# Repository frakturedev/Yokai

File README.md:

# Yokai
Yokai keyboard, a split keyboard with 5*7 column staggered keys.  Like Corne/Sofle but bigger and worse.

Most recent significant changes - Increased pinky stagger and added an additional thumb key.

Hopefully it will look a little like this:

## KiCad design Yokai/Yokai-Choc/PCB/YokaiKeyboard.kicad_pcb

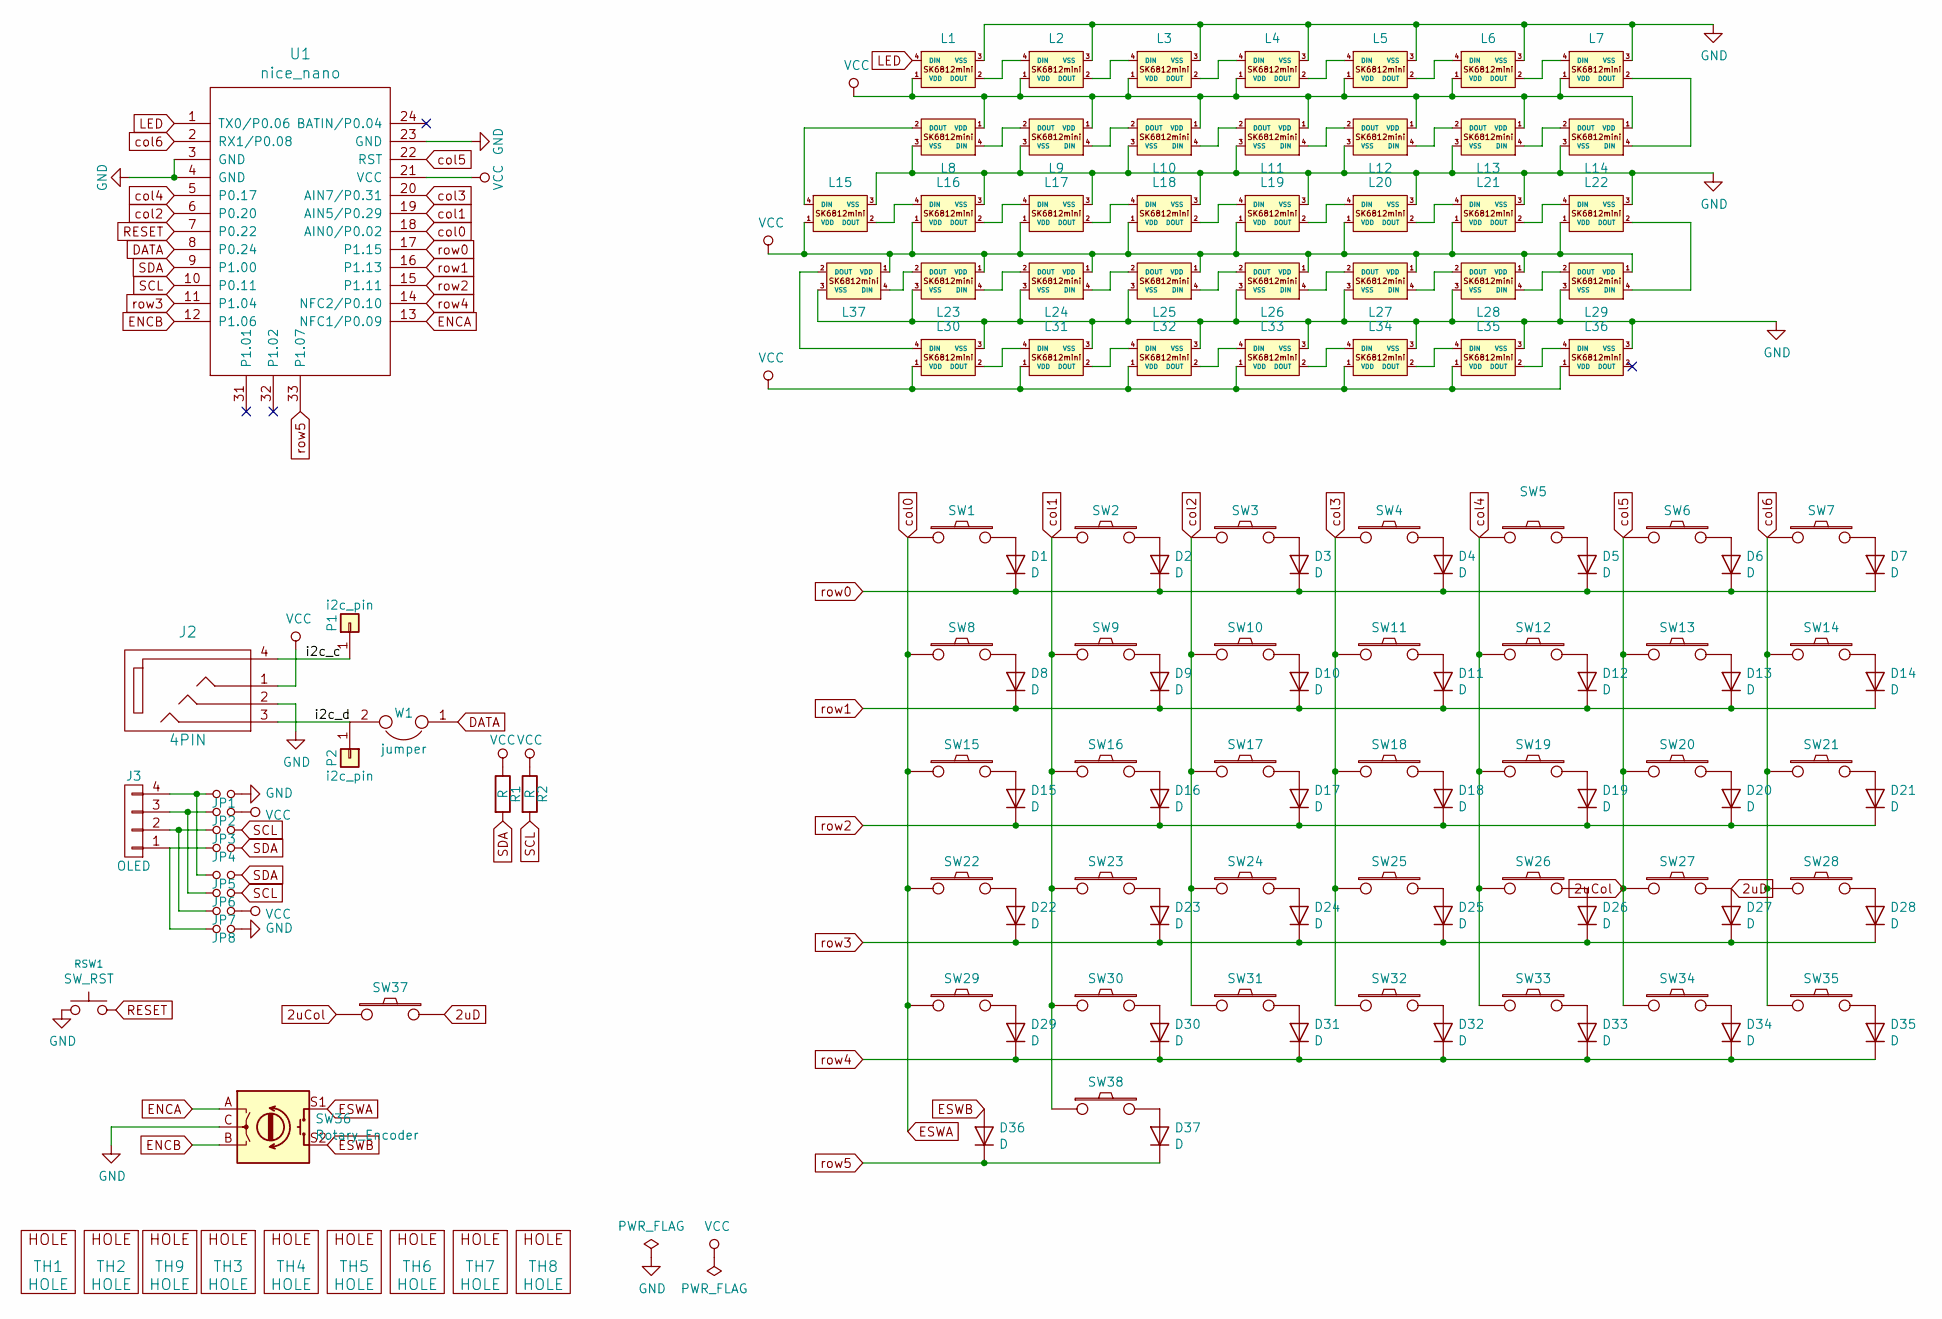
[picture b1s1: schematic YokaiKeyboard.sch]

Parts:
D1, D2, D3, D4, D5, D6, D7, D8, D9, D10, D11, D12, D13, D14, D15, D16, D17, D18, D19, D20, D21, D22, D23, D24, D25, D26, D27, D28, D29, D30, D31, D32, D33, D34, D35, D36, D37: D; smd_diode
J2: 4PIN; MJ-4PP-9
J3: OLED; OLED_4Pin
JP1, JP2, JP3, JP4, JP5, JP6, JP7, JP8: Jumper_NO_Small; Jumper
L1, L2, L3, L4, L5, L6, L7, L8, L9, L10, L11, L12, L13, L14, L15, L16, L17, L18, L19, L20, L21, L22, L23, L24, L25, L26, L27, L28, L29, L30, L31, L32, L33, L34, L35, L36, L37: LED_sk2812_SM; YS-SK6812MINI-E-DoubleSide
P1, P2: i2c_pin; 1pin_conn
R1, R2: R; RESISTOR_mini
RSW1: SW_RST; TACT_SWITCH_TVBP06
SW1, SW2, SW3, SW4, SW5, SW6, SW7, SW8, SW9, SW10, SW11, SW12, SW13, SW14, SW15, SW16, SW17, SW18, SW19, SW20, SW21, SW22, SW23, SW24, SW25, SW26, SW27, SW28, SW29, SW30, SW31, SW32, SW33, SW34, SW35, SW37, SW38: SW_PUSH-MX_W_LED; Choc_Hotswap_DoubleSide
SW36: Rotary_Encoder; RotaryEncoder_Alps_EC11E-Switch_Vertical_H20mm
TH1, TH2, TH9: HOLE; M2_HOLE_PCB
TH3, TH4, TH5, TH6, TH7, TH8: HOLE; HOLE_M2_TH
U1: nice_nano
W1: jumper; Jumper

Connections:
2uCol: SW6.1, SW13.1, SW20.1, SW27.1, SW34.1, SW37.1, U1.22 (RST)
2uD: D27.2 (A), SW27.2, SW37.2
/i2c_c: J2.4, P1.1
/i2c_d: J2.3, P2.1, W1.2
DATA: U1.8 (P0.24), W1.1
ENCA: SW36.A, U1.13 (NFC1/P0.09)
ENCB: SW36.B, U1.12 (P1.06)
ESWA: SW1.1, SW8.1, SW15.1, SW22.1, SW29.1, SW36.S1, U1.18 (AIN0/P0.02)
ESWB: D36.2 (A), SW36.S2
GND: J2.2, JP1.2, JP8.2, L1.3 (VSS), L2.3 (VSS), L3.3 (VSS), L4.3 (VSS), L5.3 (VSS), L6.3 (VSS), L7.3 (VSS), L8.3 (VSS), L9.3 (VSS), L10.3 (VSS), L11.3 (VSS), L12.3 (VSS), L13.3 (VSS), L14.3 (VSS), L15.3 (VSS), L16.3 (VSS), L17.3 (VSS), L18.3 (VSS), L19.3 (VSS), L20.3 (VSS), L21.3 (VSS), L22.3 (VSS), L23.3 (VSS), L24.3 (VSS), L25.3 (VSS), L26.3 (VSS), L27.3 (VSS), L28.3 (VSS), L29.3 (VSS), L30.3 (VSS), L31.3 (VSS), L32.3 (VSS), L33.3 (VSS), L34.3 (VSS), L35.3 (VSS), L36.3 (VSS), L37.3 (VSS), RSW1.1, SW36.C, U1.3 (GND), U1.4 (GND), U1.23 (GND)
LED: L1.4 (DIN), U1.1 (TX0/P0.06)
unnamed: D1.2 (A), SW1.2
unnamed: D2.2 (A), SW2.2
unnamed: D3.2 (A), SW3.2
unnamed: D4.2 (A), SW4.2
unnamed: D5.2 (A), SW5.2
unnamed: D6.2 (A), SW6.2
unnamed: D7.2 (A), SW7.2
unnamed: D8.2 (A), SW8.2
unnamed: D9.2 (A), SW9.2
unnamed: D10.2 (A), SW10.2
unnamed: D11.2 (A), SW11.2
unnamed: D12.2 (A), SW12.2
unnamed: D13.2 (A), SW13.2
unnamed: D14.2 (A), SW14.2
unnamed: D15.2 (A), SW15.2
unnamed: D16.2 (A), SW16.2
unnamed: D17.2 (A), SW17.2
unnamed: D18.2 (A), SW18.2
unnamed: D19.2 (A), SW19.2
unnamed: D20.2 (A), SW20.2
unnamed: D21.2 (A), SW21.2
unnamed: D22.2 (A), SW22.2
unnamed: D23.2 (A), SW23.2
unnamed: D24.2 (A), SW24.2
unnamed: D25.2 (A), SW25.2
unnamed: D26.2 (A), SW26.2
unnamed: D28.2 (A), SW28.2
unnamed: D29.2 (A), SW29.2
unnamed: D30.2 (A), SW30.2
unnamed: D31.2 (A), SW31.2
unnamed: D32.2 (A), SW32.2
unnamed: D33.2 (A), SW33.2
unnamed: D34.2 (A), SW34.2
unnamed: D35.2 (A), SW35.2
unnamed: D37.2 (A), SW38.2
unnamed: J3.1, JP4.1, JP8.1
unnamed: J3.2, JP3.1, JP7.1
unnamed: J3.3, JP2.1, JP6.1
unnamed: J3.4, JP1.1, JP5.1
unnamed: L1.2 (DOUT), L2.4 (DIN)
unnamed: L2.2 (DOUT), L3.4 (DIN)
unnamed: L3.2 (DOUT), L4.4 (DIN)
unnamed: L4.2 (DOUT), L5.4 (DIN)
unnamed: L5.2 (DOUT), L6.4 (DIN)
unnamed: L6.2 (DOUT), L7.4 (DIN)
unnamed: L8.4 (DIN), L9.2 (DOUT)
unnamed: L9.4 (DIN), L10.2 (DOUT)
unnamed: L10.4 (DIN), L11.2 (DOUT)
unnamed: L11.4 (DIN), L12.2 (DOUT)
unnamed: L12.4 (DIN), L13.2 (DOUT)
unnamed: L13.4 (DIN), L14.2 (DOUT)
unnamed: L7.2 (DOUT), L14.4 (DIN)
unnamed: L15.2 (DOUT), L16.4 (DIN)
unnamed: L8.2 (DOUT), L15.4 (DIN)
unnamed: L16.2 (DOUT), L17.4 (DIN)
unnamed: L17.2 (DOUT), L18.4 (DIN)
unnamed: L18.2 (DOUT), L19.4 (DIN)
unnamed: L19.2 (DOUT), L20.4 (DIN)
unnamed: L20.2 (DOUT), L21.4 (DIN)
unnamed: L21.2 (DOUT), L22.4 (DIN)
unnamed: L22.2 (DOUT), L29.4 (DIN)
unnamed: L23.2 (DOUT), L37.4 (DIN)
unnamed: L23.4 (DIN), L24.2 (DOUT)
unnamed: L24.4 (DIN), L25.2 (DOUT)
unnamed: L25.4 (DIN), L26.2 (DOUT)
unnamed: L26.4 (DIN), L27.2 (DOUT)
unnamed: L27.4 (DIN), L28.2 (DOUT)
unnamed: L28.4 (DIN), L29.2 (DOUT)
unnamed: L30.2 (DOUT), L31.4 (DIN)
unnamed: L30.4 (DIN), L37.2 (DOUT)
unnamed: L31.2 (DOUT), L32.4 (DIN)
unnamed: L32.2 (DOUT), L33.4 (DIN)
unnamed: L33.2 (DOUT), L34.4 (DIN)
unnamed: L34.2 (DOUT), L35.4 (DIN)
unnamed: L35.2 (DOUT), L36.4 (DIN)
RESET: RSW1.2, U1.7 (P0.22)
SCL: JP3.2, JP6.2, R2.2, U1.10 (P0.11)
SDA: JP4.2, JP5.2, R1.2, U1.9 (P1.00)
VCC: J2.1, JP2.2, JP7.2, L1.1 (VDD), L2.1 (VDD), L3.1 (VDD), L4.1 (VDD), L5.1 (VDD), L6.1 (VDD), L7.1 (VDD), L8.1 (VDD), L9.1 (VDD), L10.1 (VDD), L11.1 (VDD), L12.1 (VDD), L13.1 (VDD), L14.1 (VDD), L15.1 (VDD), L16.1 (VDD), L17.1 (VDD), L18.1 (VDD), L19.1 (VDD), L20.1 (VDD), L21.1 (VDD), L22.1 (VDD), L23.1 (VDD), L24.1 (VDD), L25.1 (VDD), L26.1 (VDD), L27.1 (VDD), L28.1 (VDD), L29.1 (VDD), L30.1 (VDD), L31.1 (VDD), L32.1 (VDD), L33.1 (VDD), L34.1 (VDD), L35.1 (VDD), L36.1 (VDD), L37.1 (VDD), R1.1, R2.1, U1.21 (VCC)
col1: SW2.1, SW9.1, SW16.1, SW23.1, SW30.1, SW38.1, U1.19 (AIN5/P0.29)
col2: SW3.1, SW10.1, SW17.1, SW24.1, SW31.1, U1.6 (P0.20)
col3: SW4.1, SW11.1, SW18.1, SW25.1, SW32.1, U1.20 (AIN7/P0.31)
col4: SW5.1, SW12.1, SW19.1, SW26.1, SW33.1, U1.5 (P0.17)
col6: SW7.1, SW14.1, SW21.1, SW28.1, SW35.1, U1.2 (RX1/P0.08)
row0: D1.1 (K), D2.1 (K), D3.1 (K), D4.1 (K), D5.1 (K), D6.1 (K), D7.1 (K), U1.17 (P1.15)
row1: D8.1 (K), D9.1 (K), D10.1 (K), D11.1 (K), D12.1 (K), D13.1 (K), D14.1 (K), U1.16 (P1.13)
row2: D15.1 (K), D16.1 (K), D17.1 (K), D18.1 (K), D19.1 (K), D20.1 (K), D21.1 (K), U1.15 (P1.11)
row3: D22.1 (K), D23.1 (K), D24.1 (K), D25.1 (K), D26.1 (K), D27.1 (K), D28.1 (K), U1.11 (P1.04)
row4: D29.1 (K), D30.1 (K), D31.1 (K), D32.1 (K), D33.1 (K), D34.1 (K), D35.1 (K), U1.14 (NFC2/P0.10)
row5: D36.1 (K), D37.1 (K), U1.33 (P1.07)

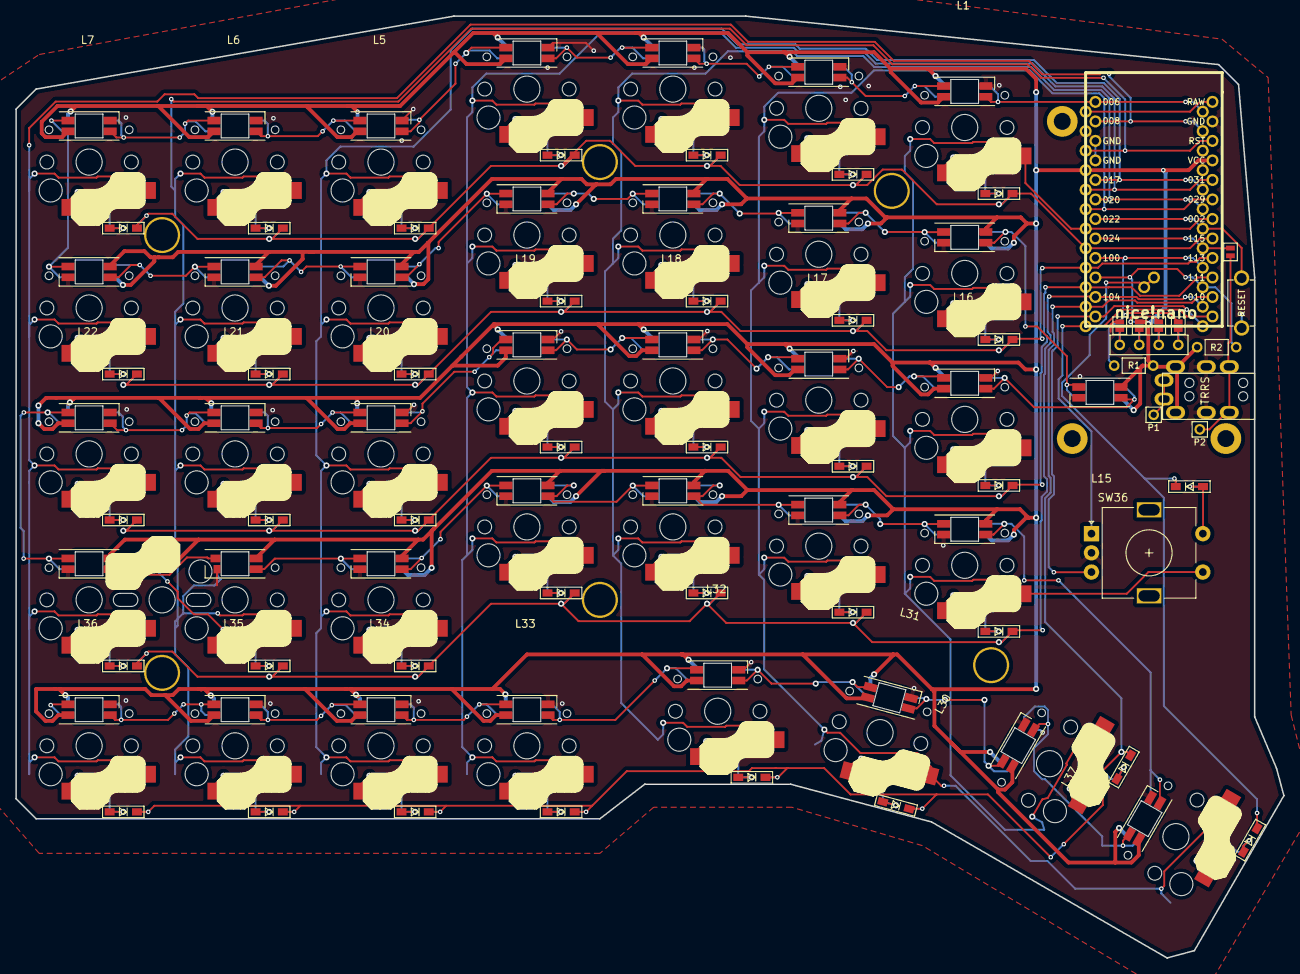
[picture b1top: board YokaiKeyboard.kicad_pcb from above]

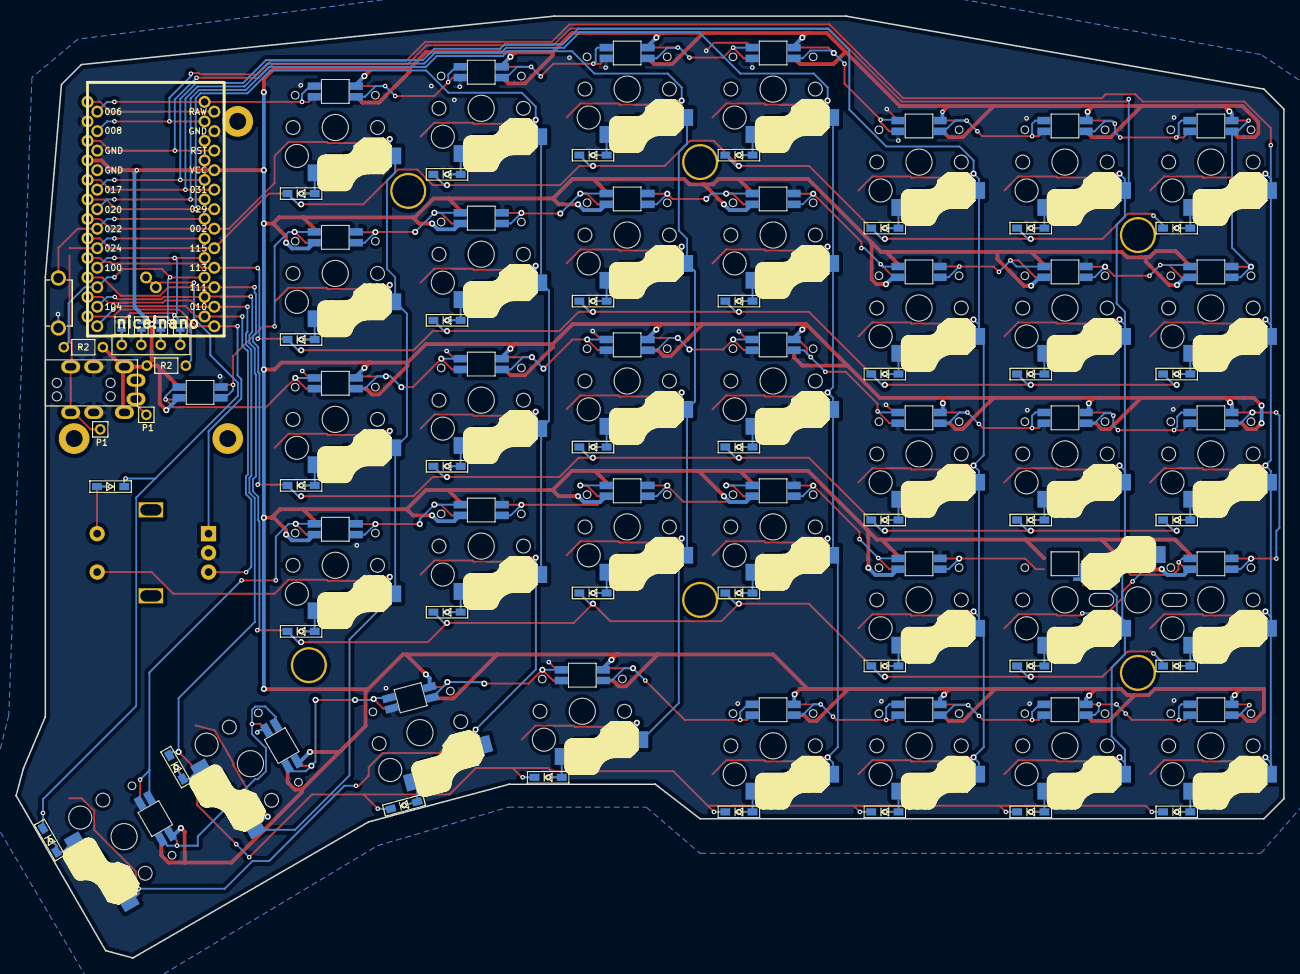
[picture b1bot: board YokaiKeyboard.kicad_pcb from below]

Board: 2 copper layers, 165.1 x 122.6 mm, 138 parts (4 on the bottom side), 101 nets.

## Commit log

2021-09-04 First Upload
    First
2021-09-18 Add files via upload
    *Increased pinky stagger
    *Inverted stabilizer cutouts
    *Added additional thumb key
    *Minor footprint changes
